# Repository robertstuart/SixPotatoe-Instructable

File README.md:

# SixPotatoe-Instructable
This repository contains all of the code and documentation needed to construct SixPotatoe, a high-performance inverted-pendulum robot.   A complete tutorial for building this robot can be found at: https://www.instructables.com/id/Build-a-High-Performance-Inverted-Pendulum-Robot/.

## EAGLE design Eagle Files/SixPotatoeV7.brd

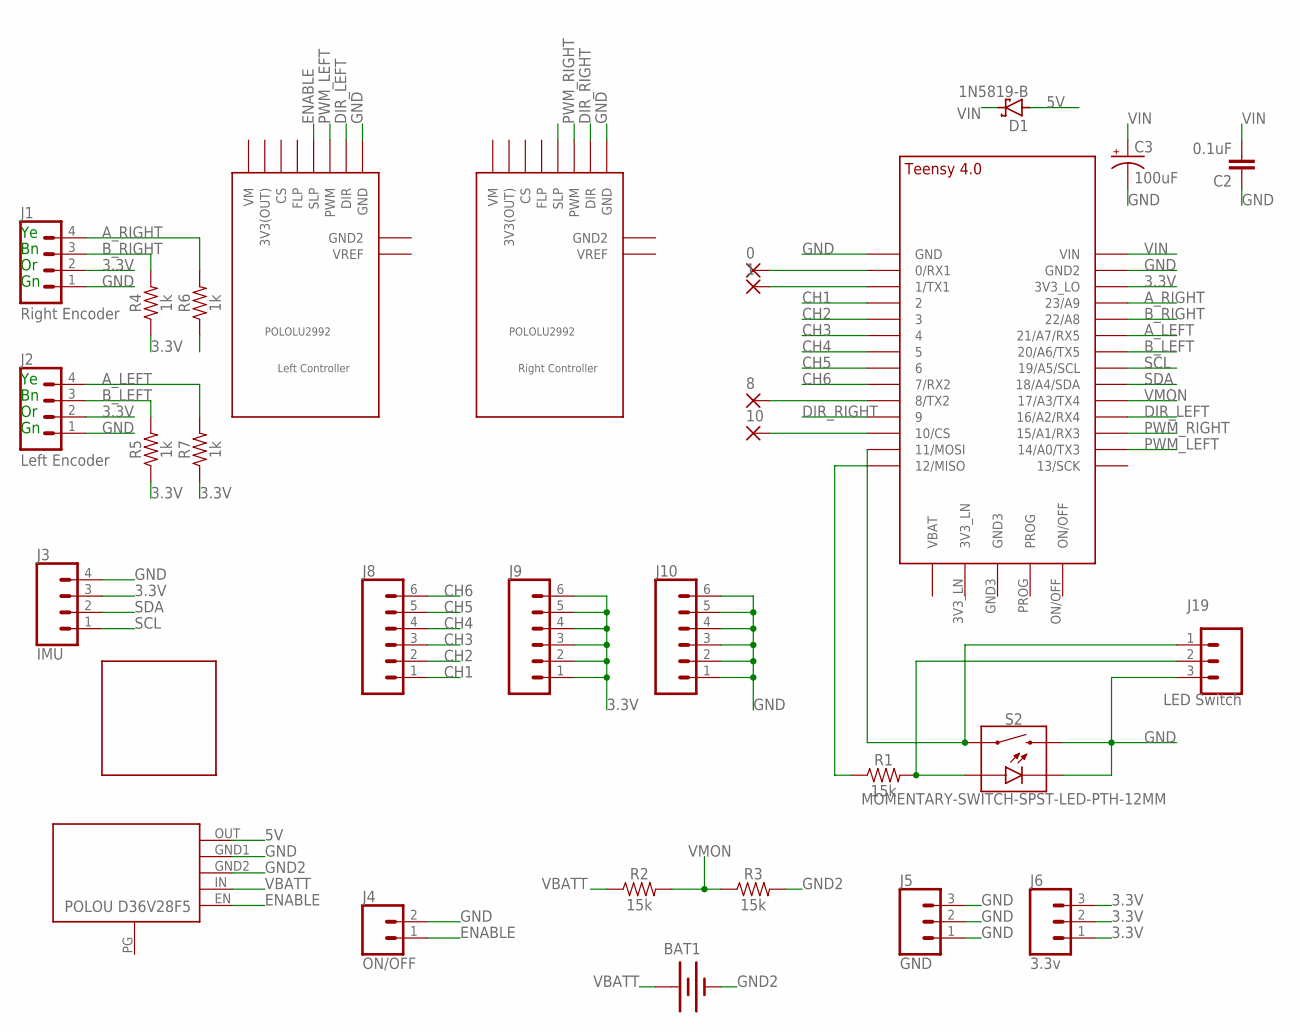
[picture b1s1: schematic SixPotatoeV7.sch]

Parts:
0, 1, 8, 10: 2,15/1,0
BAT1: XT60_MALE; XT60
C2: 0.1uF; CAP-PTH-SMALL-KIT
C3: 100uF; CPOL-RADIAL-2.5MM-6.5MM
D1: 1N5819-B; DO41-7.6
J1, J2: CONN_04; 1X04
J3: IMU; 1X04
J4: ON/OFF; 1X02
J5: GND; 1X03
J6: 3.3v; 1X03
J8, J9, J10: CONN_06NO_SILK_FEMALE_PTH; 1X06_NO_SILK
J19: CONN_03; 1X03
R1, R2, R3: 15k; AXIAL-0.3
R4, R5, R6, R7: 1k; AXIAL-0.3
S2: MOMENTARY-SWITCH-SPST-LED-PTH-12MM; TACTILE_SWITCH_LED_PTH_12MM
U$1: TEENSY_4.0
U$2: Left Controller; POLOLU2992_2
U$3: Right Controller; POLOLU2992_2
U$4: POLOU3782
U$5: SEN15335_NO_PTH

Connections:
3.3V: J1.2, J2.2, J3.3, J6.1, J6.2, J6.3, J9.1, J9.2, J9.3, J9.4, J9.5, J9.6, R4.P$1 (1), R5.P$1 (1), R6.P$1 (1), R7.P$1 (1), U$1.3V3_LO
5V: D1.A, U$4.OUT
A_LEFT: J2.4, R7.P$2 (2), U$1.21/A7 (21/A7/RX5)
A_RIGHT: J1.4, R6.P$2 (2), U$1.23/A9
B_LEFT: J2.3, R5.P$2 (2), U$1.20/A6 (20/A6/TX5)
B_RIGHT: J1.3, R4.P$2 (2), U$1.22/A8
CH1: J8.1, U$1.2
CH2: J8.2, U$1.3/CANTX (3)
CH3: J8.3, U$1.4/CANRX (4)
CH4: J8.4, U$1.5
CH5: J8.5, U$1.6
CH6: J8.6, U$1.7 (7/RX2)
DIR_LEFT: U$1.16/A2 (16/A2/RX4), U$2.DIR
DIR_RIGHT: U$1.9/CS (9), U$3.DIR
ENABLE: J4.1, U$2.SLP, U$3.SLP, U$4.EN
GND: C2.1, C3.2 (-), J1.1, J2.1, J3.4, J4.2, J5.1, J5.2, J5.3, J10.1, J10.2, J10.3, J10.4, J10.5, J10.6, J19.3, S2.2, S2.C, U$1.GND, U$1.GND2, U$2.GND, U$3.GND, U$4.GND1
GND2: BAT1.-, R3.P$2 (2), U$4.GND2
unnamed: 0.1, U$1.0/RX (0/RX1)
unnamed: J19.2, R1.P$2 (2), S2.A
unnamed: R1.P$1 (1), U$1.12/MISO
unnamed: J19.1, S2.4 (1), U$1.11/MOSI
unnamed: 1.1, U$1.1/TX (1/TX1)
unnamed: 10.1, U$1.10/CS
unnamed: 8.1, U$1.8 (8/TX2)
PWM_LEFT: U$1.14/A0 (14/A0/TX3), U$2.PWM
PWM_RIGHT: U$1.15/A1 (15/A1/RX3), U$3.PWM
SCL: J3.1, U$1.19/A5/SCL
SDA: J3.2, U$1.18/A4/SDA
VBATT: BAT1.+, R2.P$1 (1), U$4.IN
VIN: C2.2, C3.1 (+), D1.C, U$1.VIN
VMON: R2.P$2 (2), R3.P$1 (1), U$1.17/A3 (17/A3/TX4)

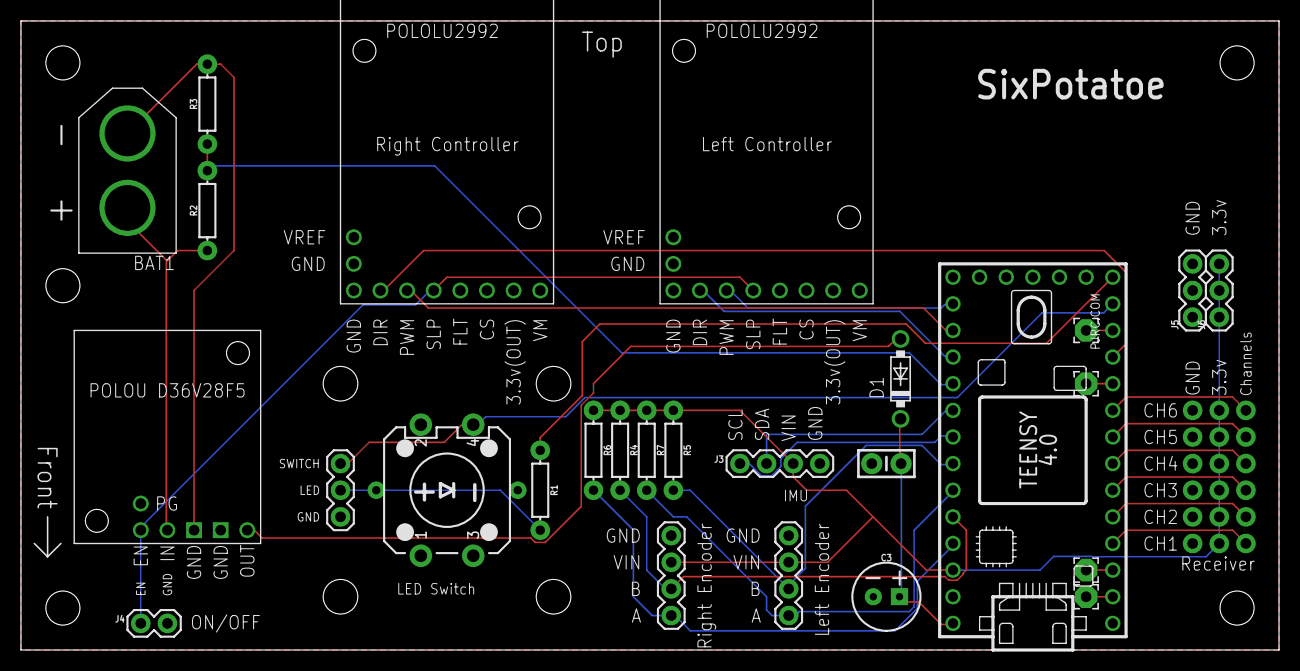
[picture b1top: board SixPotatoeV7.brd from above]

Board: 2 copper layers, 120.0 x 60.0 mm, 31 parts (1 on the bottom side), 31 nets.

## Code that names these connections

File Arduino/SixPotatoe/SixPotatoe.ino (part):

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/*****************************************************************************-
 *  Pin definitions
 *****************************************************************************/
const int PWM_LEFT_PIN    = 14;
const int PWM_RIGHT_PIN   = 15;
const int DIR_LEFT_PIN    = 16;
const int DIR_RIGHT_PIN   =  9;

const int ENC_B_LEFT_PIN  = 20;
const int ENC_A_LEFT_PIN  = 21;
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
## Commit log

2020-05-11 Initial commit of the Arduino code
2020-05-11 Add drawings
2020-05-11 Add Eagle files
2020-05-12 Fixed turns
2020-05-20 Video completed
    Also, excess code removed, first routes checked out.
2020-05-23 Intermediate checkin
2020-05-25 Updated for V7 boards
2020-05-27 Instructable docs
2020-06-03 New PCB pin defs
    Also battery monitoring
2020-06-04 Version 7 Gerber files for PCB
2020-06-07 Checkin before encoder equalizing added
2020-06-09 Revised drawings
2020-06-26 Add encoder equalization
    Encoder now used last 4 ticks for kph. This checkin is before changeds to be made for 612 RPM motor.
2020-06-26 612 RPM motor working
2020-07-08 Before isr mods
    This is a check-in before the new isr mods are added. The actual interrupt times are put in a buffer and read out by the readSpeed?() routines.
2020-07-11 Release 10-Jun-2020
    Many fixes, mods & enhancements.
2020-07-11 Revert "Release 10-Jun-2020"
    This reverts commit 6ae50b53aa5354b7f7f80889ba46ecac2c478f51.
2020-07-11 Release 10-Jul-2020
2020-07-11 Final Release 10-Jul-2020
2020-07-23 New faster IMU reads
2020-08-05 Low speed steering
2020-09-03 New Ch4 values
    Recent Dumborc controllers have a smaller range for the CH4 values. These new values will work on all controllers.
2020-09-20 Battery events
    Fixed the battery() routine so that it adjusts properly for different battery voltages.

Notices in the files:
parts and their libraries:
SparkFun-Connectors: Licensing: Creative Commons ShareAlike 4.0 International - https://creativecommons.org/licenses/by-sa/4.0
